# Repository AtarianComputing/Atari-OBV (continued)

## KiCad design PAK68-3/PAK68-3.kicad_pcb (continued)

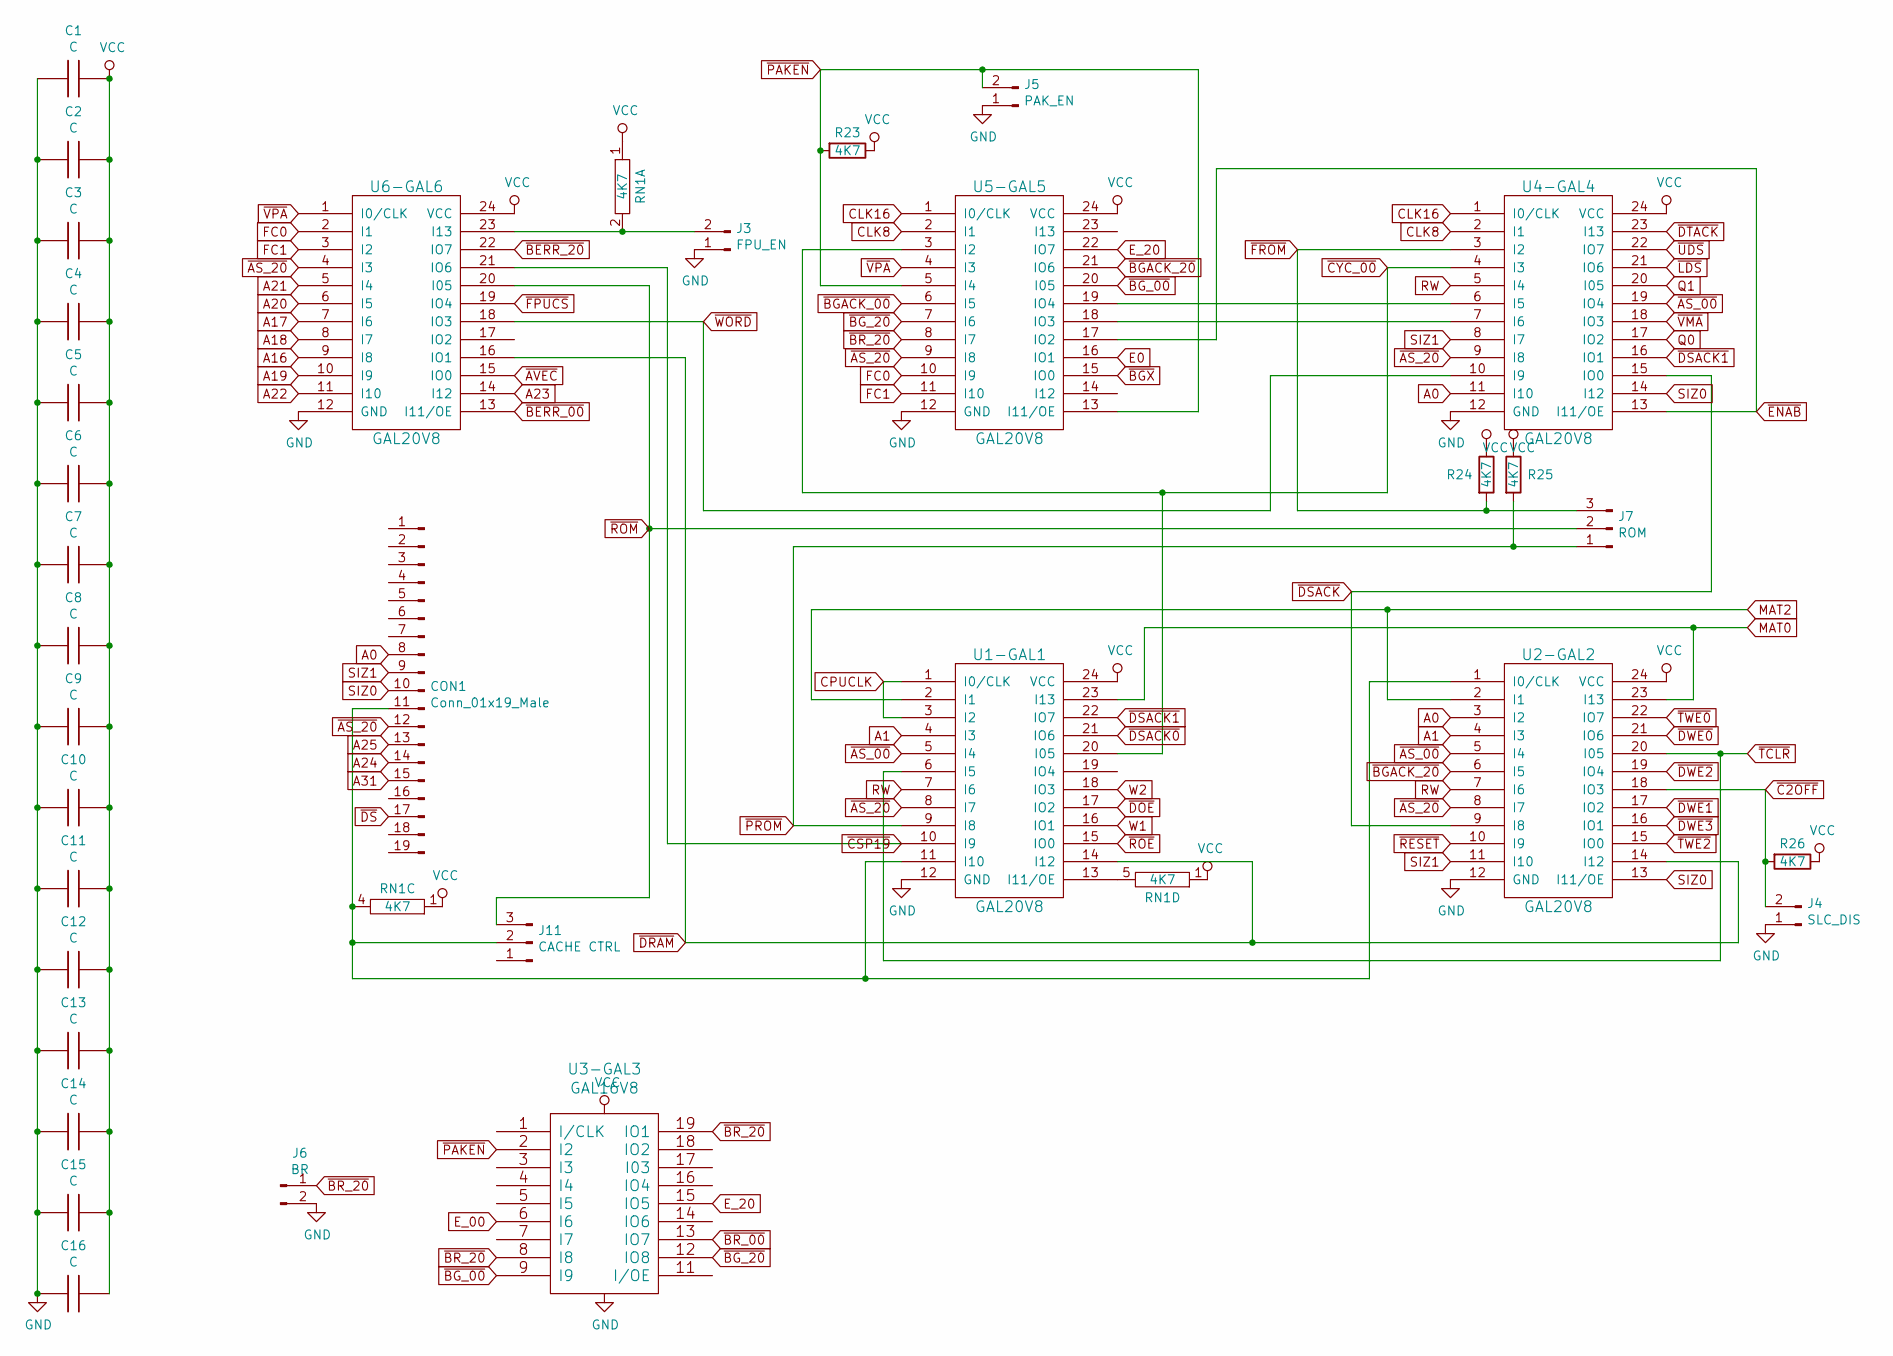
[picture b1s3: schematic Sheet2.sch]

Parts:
C1, C2, C3, C4, C5, C6, C7, C8, C9, C10, C11, C12, C13, C14, C15, C16: C; C_Rect_L4.0mm_W2.5mm_P2.50mm
CON1: Conn_01x19_Male; Socket_Strip_Straight_1x19_Pitch2.54mm
J3: FPU_EN; Socket_Strip_Straight_1x02_Pitch2.54mm
J4: SLC_DIS; Socket_Strip_Straight_1x02_Pitch2.54mm
J5: PAK_EN; Socket_Strip_Straight_1x02_Pitch2.54mm
J6: BR; Socket_Strip_Straight_1x02_Pitch2.54mm
J7: ROM; Socket_Strip_Straight_1x03_Pitch2.54mm
J11: CACHE CTRL; Socket_Strip_Straight_1x03_Pitch2.54mm
R23, R24, R25, R26: 4K7; R_Axial_DIN0207_L6.3mm_D2.5mm_P10.16mm_Horizontal
RN1: 4K7; R_Array_SIP9
U1-GAL1, U2-GAL2, U4-GAL4, U5-GAL5, U6-GAL6: GAL20V8; DIP-24_W7.62mm
U3-GAL3: GAL16V8; DIP-20_W7.62mm

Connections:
A0: CON1.8, U2-GAL2.3 (I2), U4-GAL4.11 (I10); also elsewhere on the board
A1: U1-GAL1.4 (I3), U2-GAL2.4 (I3); also elsewhere on the board
A16: U6-GAL6.9 (I8); also elsewhere on the board
A17: U6-GAL6.7 (I6); also elsewhere on the board
A18: U6-GAL6.8 (I7); also elsewhere on the board
A19: U6-GAL6.10 (I9); also elsewhere on the board
A20: U6-GAL6.6 (I5); also elsewhere on the board
A21: U6-GAL6.5 (I4); also elsewhere on the board
A22: U6-GAL6.11 (I10); also elsewhere on the board
A23: U6-GAL6.14 (I12); also elsewhere on the board
A24: CON1.14; also elsewhere on the board
A25: CON1.13; also elsewhere on the board
A31: CON1.15; also elsewhere on the board
CLK8: U4-GAL4.2 (I1), U5-GAL5.2 (I1); also elsewhere on the board
CLK16: U4-GAL4.1 (I0/CLK), U5-GAL5.1 (I0/CLK); also elsewhere on the board
CPUCLK: U1-GAL1.1 (I0/CLK), U1-GAL1.3 (I2); also elsewhere on the board
E0: U5-GAL5.16 (IO1)
E_00: U3-GAL3.6 (I6); also elsewhere on the board
E_20: U3-GAL3.15 (IO5), U5-GAL5.22 (IO7); also elsewhere on the board
FC0: U5-GAL5.10 (I9), U6-GAL6.2 (I1); also elsewhere on the board
FC1: U5-GAL5.11 (I10), U6-GAL6.3 (I2); also elsewhere on the board
GND: C1.2, C2.2, C3.2, C4.2, C5.2, C6.2, C7.2, C8.2, C9.2, C10.2, C11.2, C12.2, C13.2, C14.2, C15.2, C16.2, J3.1, J4.1, J5.1, J6.2, U1-GAL1.12 (GND), U2-GAL2.12 (GND), U3-GAL3.10 (GND), U4-GAL4.12 (GND), U5-GAL5.12 (GND), U6-GAL6.12 (GND); also elsewhere on the board
MAT0: U1-GAL1.23 (I13), U2-GAL2.23 (I13); also elsewhere on the board
MAT2: U1-GAL1.2 (I1), U2-GAL2.2 (I1); also elsewhere on the board
unnamed: CON1.11, J11.2, RN1.4, U1-GAL1.11 (I10), U2-GAL2.1 (I0/CLK)
unnamed: J3.2, RN1.2, U6-GAL6.23 (I13)
unnamed: RN1.5, U1-GAL1.13 (I11/OE)
unnamed: U4-GAL4.6 (I5), U5-GAL5.19 (IO4)
unnamed: U4-GAL4.7 (I6), U5-GAL5.18 (IO3)
Q0: U4-GAL4.17 (IO2)
Q1: U4-GAL4.20 (I05)
RW: U1-GAL1.7 (I6), U2-GAL2.7 (I6), U4-GAL4.5 (I4); also elsewhere on the board
SIZ0: CON1.10, U2-GAL2.13 (I11/OE), U4-GAL4.14 (I12); also elsewhere on the board
SIZ1: CON1.9, U2-GAL2.11 (I10), U4-GAL4.8 (I7); also elsewhere on the board
VCC: C1.1, C2.1, C3.1, C4.1, C5.1, C6.1, C7.1, C8.1, C9.1, C10.1, C11.1, C12.1, C13.1, C14.1, C15.1, C16.1, R23.1, R24.1, R25.1, R26.1, RN1.1, U1-GAL1.24 (VCC), U2-GAL2.24 (VCC), U3-GAL3.20 (VCC), U4-GAL4.24 (VCC), U5-GAL5.24 (VCC), U6-GAL6.24 (VCC); also elsewhere on the board
W1: U1-GAL1.16 (IO1)
W2: U1-GAL1.18 (IO3)
~AS_00~: U1-GAL1.5 (I4), U2-GAL2.5 (I4), U4-GAL4.19 (IO4); also elsewhere on the board
~AS_20~: CON1.12, U1-GAL1.8 (I7), U2-GAL2.8 (I7), U4-GAL4.9 (I8), U5-GAL5.9 (I8), U6-GAL6.4 (I3); also elsewhere on the board
~AVEC~: U6-GAL6.15 (IO0); also elsewhere on the board
~BERR_00~: U6-GAL6.13 (I11/OE); also elsewhere on the board
~BERR_20~: U6-GAL6.22 (IO7); also elsewhere on the board
~BGACK_00~: U5-GAL5.6 (I5); also elsewhere on the board
~BGACK_20~: U2-GAL2.6 (I5), U5-GAL5.21 (IO6); also elsewhere on the board
~BGX~: U5-GAL5.15 (IO0)
~BG_00~: U3-GAL3.9 (I9), U5-GAL5.20 (I05); also elsewhere on the board
~BG_20~: U3-GAL3.12 (IO8), U5-GAL5.7 (I6); also elsewhere on the board
~BR_00~: U3-GAL3.13 (IO7); also elsewhere on the board
~BR_20~: J6.1, U3-GAL3.8 (I8), U3-GAL3.19 (IO1), U5-GAL5.8 (I7); also elsewhere on the board
~C2OFF~: J4.2, R26.2, U2-GAL2.18 (IO3)
~CSP19~: U1-GAL1.10 (I9), U6-GAL6.21 (IO6)
~CYC_00~: U1-GAL1.20 (I05), U4-GAL4.4 (I3), U5-GAL5.3 (I2)
~DOE~: U1-GAL1.17 (IO2); also elsewhere on the board
~DRAM~: U1-GAL1.14 (I12), U2-GAL2.14 (I12), U6-GAL6.16 (IO1)
~DSACK0~: U1-GAL1.21 (IO6); also elsewhere on the board
~DSACK1~: U1-GAL1.22 (IO7), U4-GAL4.16 (IO1); also elsewhere on the board
~DSACK~: U2-GAL2.9 (I8), U4-GAL4.15 (IO0)
~DS~: CON1.17; also elsewhere on the board
~DTACK~: U4-GAL4.23 (I13); also elsewhere on the board
~DWE0~: U2-GAL2.21 (IO6); also elsewhere on the board
~DWE1~: U2-GAL2.17 (IO2); also elsewhere on the board
~DWE2~: U2-GAL2.19 (IO4); also elsewhere on the board
~DWE3~: U2-GAL2.16 (IO1); also elsewhere on the board
~ENAB~: U4-GAL4.13 (I11/OE), U5-GAL5.17 (IO2)
~FPUCS~: U6-GAL6.19 (IO4); also elsewhere on the board
~FROM~: J7.3, R24.2, U4-GAL4.3 (I2)
~LDS~: U4-GAL4.21 (IO6); also elsewhere on the board
~PAKEN~: J5.2, R23.2, U3-GAL3.2 (I2), U5-GAL5.5 (I4), U5-GAL5.13 (I11/OE)
~PROM~: J7.1, R25.2, U1-GAL1.9 (I8)
~RESET~: U2-GAL2.10 (I9); also elsewhere on the board
~ROE~: U1-GAL1.15 (IO0); also elsewhere on the board
~ROM~: J7.2, J11.3, U6-GAL6.20 (I05)
~TCLR~: U1-GAL1.6 (I5), U2-GAL2.20 (I05); also elsewhere on the board
~TWE0~: U2-GAL2.22 (IO7); also elsewhere on the board
~TWE2~: U2-GAL2.15 (IO0); also elsewhere on the board
~UDS~: U4-GAL4.22 (IO7); also elsewhere on the board
~VMA~: U4-GAL4.18 (IO3); also elsewhere on the board
~VPA~: U5-GAL5.4 (I3), U6-GAL6.1 (I0/CLK); also elsewhere on the board
~WORD~: U4-GAL4.10 (I9), U6-GAL6.18 (IO3)

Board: 2 copper layers, 87 parts (0 on the bottom side), 141 nets, no tracks yet.

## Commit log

2018-12-16 Initial commit
    Cleaned up version
2018-12-23 Initial KiCad commit
